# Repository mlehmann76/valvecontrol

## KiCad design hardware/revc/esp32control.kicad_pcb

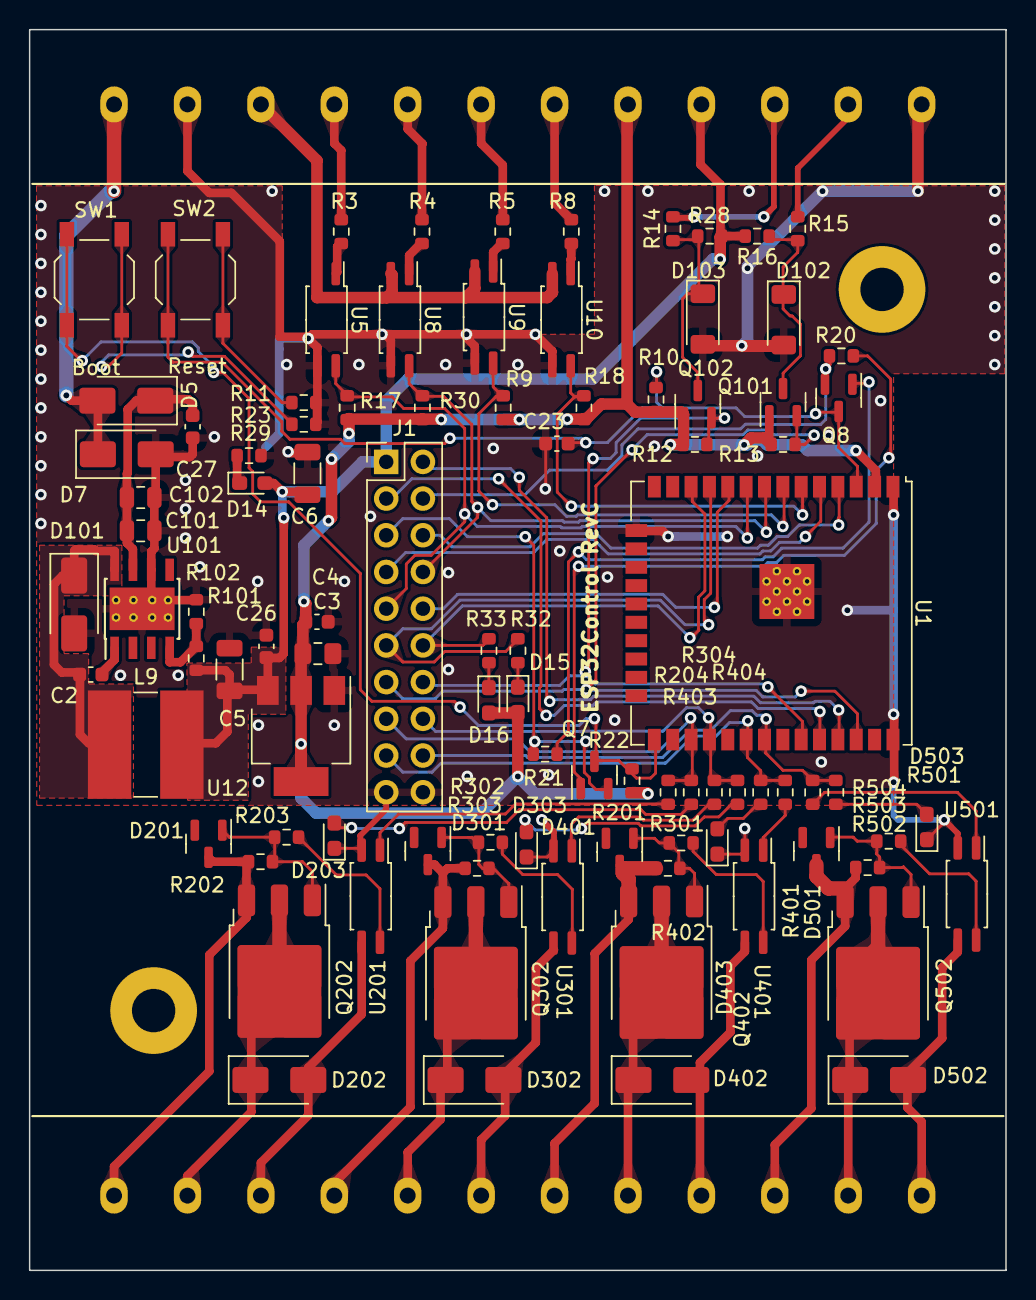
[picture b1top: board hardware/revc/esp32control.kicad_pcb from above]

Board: 2 copper layers, 67.6 x 85.9 mm, 95 parts (0 on the bottom side), 77 nets.

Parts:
C2: 10n 50V; C_0603_1608Metric
C3: 10u 25V; C_0805_2012Metric_Pad1.18x1.45mm_HandSolder
C4, C26, C27: 100n 50V; C_0603_1608Metric
C5, C6: 47u 10V; C_1206_3216Metric
C23: 1u 25V; C_0603_1608Metric
C101, C102: 10u 50V; C_0805_2012Metric
D5, D101, D202, D302, D402, D502: SS34; D_SMA
D7: SMAJ26CAQ; D_SMA
D14, D15, D16, D203, D303, D403, D503: red; LED_0603_1608Metric_Pad1.05x0.95mm_HandSolder
D102, D103: ZMM5V6-M; D_MiniMELF
D201, D301, D401, D501: BZX84C10; SOT-23
J1: Conn_02x10_Odd_Even; PinHeader_2x10_P2.54mm_Vertical
L9: 22u; L_Ferrocore_DLG-0705
Q7, Q8: MMBT3904; SOT-23
Q101, Q102: 2N7002; SOT-23
Q202, Q302, Q402, Q502: HSU4113; TO-252-3_TabPin2
R3, R4, R5, R8: 1k5; R_0603_1608Metric
R9, R10, R12, R13, R16, R17, R18, R20, R21, R22, R28, R30: 10k; R_0603_1608Metric
R11, R14, R15, R23: 100; R_0603_1608Metric
R29, R32, R33, R201, R202, R203, R204, R301, R302, R303, R304, R401, R402, R403, R404, R501, R502, R503, R504: 1k; R_0603_1608Metric
R101: 12k; R_0603_1608Metric
R102: 3k9; R_0603_1608Metric
SW1: Boot; SW_SPST_TL3342
SW2: Reset; SW_SPST_TL3342
U1: ESP32-WROOM; ESP32-WROOM-32UE
U5, U8, U9, U10, U201, U301, U401, U501: EL3H7; SOP-4_4.4x2.6mm_P1.27mm
U11: HUT4; CB_HUT_4
U12: AMS1117-3.3; SOT-223-3_TabPin2
U101: TPS5430DDA; TI_SO-PowerPAD-8_ThermalVias

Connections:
+3V3: C3.1, C4.1, D15.2 (A), D16.2 (A), Q101.1 (G), Q102.1 (G), R9.2, R10.2, R12.2, R13.2, R17.2, R18.2, R22.2, R30.2, U1.2 (3V3), U11.20, U12.2 (VO)
+5V: C5.1, C6.1, C26.1, D14.2 (A), J1.1, L9.2, R16.2, R28.2, R101.1, U11.21, U12.3 (VI)
+24V: C27.1, C101.1, C102.1, D5.1 (K), U101.7 (VIN)
/CH1: J1.15, R201.2, R204.2, U1.27 (IO16)
/CH2: J1.16, R301.2, R304.2, U1.28 (IO17)
/CH3: J1.17, R401.2, R404.2, U1.30 (IO18)
/CH4: J1.18, R501.2, R504.2, U1.31 (IO19)
/DTR: J1.5, Q7.2 (E), R21.1
/IN1: R3.2, U11.16
/IN2: R4.2, U11.17
/IN3: R5.2, U11.18
/IN4: R8.2, U11.19
/IO25: J1.10, U1.10 (IO25)
/IO26: J1.11, R32.1, U1.11 (IO26)
/IO27: J1.12, R33.1, U1.12 (IO27)
/IO32: J1.8, R30.1, U1.8 (IO32), U8.4
/IO33: J1.9, R17.1, U1.9 (IO33), U5.4
/IO34: R18.1, U1.6 (IO34), U10.4
/IO35: R9.1, U1.7 (IO35), U9.4
/IO36: J1.6, U1.4 (SENSOR_VP)
/IO39: J1.7, U1.5 (SENSOR_VN)
/OUT1: D202.1 (K), Q202.2 (D), U11.2
/OUT2: D302.1 (K), Q302.2 (D), U11.5
/OUT3: D402.1 (K), Q402.2 (D), U11.8
/OUT4: D502.1 (K), Q502.2 (D), U11.11
/PH: C2.2, D101.1 (K), L9.1, U101.8 (PH)
/RTS: J1.4, Q8.2 (E), R20.1
/RXD0: J1.3, U1.34 (RXD0)
/SCL: J1.13, Q101.2 (S), R13.1, U1.36 (IO22)
/SCL_EXT: D102.1 (K), Q101.3 (D), R15.1, R16.1
/SDA: J1.14, Q102.2 (S), R12.1, U1.33 (IO21)
/SDA_EXT: D103.1 (K), Q102.3 (D), R14.1, R28.1
/TXD0: J1.2, U1.35 (TXD0)
/dig_output/GNDA: D202.2 (A), U11.3, U201.3
/dig_output/Vin: D201.3 (K), Q202.3 (S), R202.1, U11.1
/nBoot: Q7.3 (C), R22.1, SW1.2, U1.25 (IO0)
/nReset: C23.1, Q8.3 (C), R10.1, SW2.2, U1.3 (EN)
/sheet5C1F9DE2/GNDA: D402.2 (A), U11.9, U401.3
/sheet5C1F9DE2/Vin: D401.3 (K), Q402.3 (S), R402.1, U11.7
/sheet5C1F9DE3/GNDA: D502.2 (A), U11.12, U501.3
/sheet5C1F9DE3/Vin: D501.3 (K), Q502.3 (S), R502.1, U11.10
/sheet5C1F370F/GNDA: D302.2 (A), U11.6, U301.3
/sheet5C1F370F/Vin: D301.3 (K), Q302.3 (S), R302.1, U11.4
GND: C3.2, C4.2, C5.2, C6.2, C23.2, C26.2, C27.2, C101.2, C102.2, D7.2, D101.2 (A), D102.2 (A), D103.2 (A), D203.1 (K), D303.1 (K), D403.1 (K), D503.1 (K), J1.19, J1.20, R11.2, R23.2, R29.1, R102.2, U1.1 (GND), U1.15 (GND), U1.38 (GND), U1.39 (GND-PAD), U5.3, U8.3, U9.3, U10.3, U11.14, U11.24, U12.1 (GND), U101.6 (GND), U101.9 (GNDPAD), U201.2, U301.2, U401.2, U501.2
unnamed: D14.1 (K), R29.2
unnamed: D15.1 (K), R32.2
unnamed: D16.1 (K), R33.2
unnamed: D201.1 (A), Q202.1 (G), R202.2, R203.2
unnamed: D203.2 (A), R204.1
unnamed: D301.1 (A), Q302.1 (G), R302.2, R303.2
unnamed: D303.2 (A), R304.1
unnamed: D401.1 (A), Q402.1 (G), R402.2, R403.2
unnamed: D403.2 (A), R404.1
unnamed: D501.1 (A), Q502.1 (G), R502.2, R503.2
unnamed: D503.2 (A), R504.1
unnamed: Q7.1 (B), R20.2
unnamed: Q8.1 (B), R21.2
unnamed: R3.1, U5.1
unnamed: R4.1, U8.1
unnamed: R5.1, U9.1
unnamed: R8.1, U10.1
unnamed: R11.1, SW2.1
unnamed: R14.2, U11.22
unnamed: R15.2, U11.23
unnamed: R23.1, SW1.1
unnamed: R201.1, U201.1
unnamed: R203.1, U201.4
unnamed: R301.1, U301.1
unnamed: R303.1, U301.4
unnamed: R401.1, U401.1
unnamed: R403.1, U401.4
unnamed: R501.1, U501.1
unnamed: R503.1, U501.4
unnamed: C2.1, U101.1 (BOOT)
unnamed: R101.2, R102.1, U101.4 (VSENSE)
VCOM: U5.2, U8.2, U9.2, U10.2, U11.15
VD: D5.2 (A), D7.1, U11.13

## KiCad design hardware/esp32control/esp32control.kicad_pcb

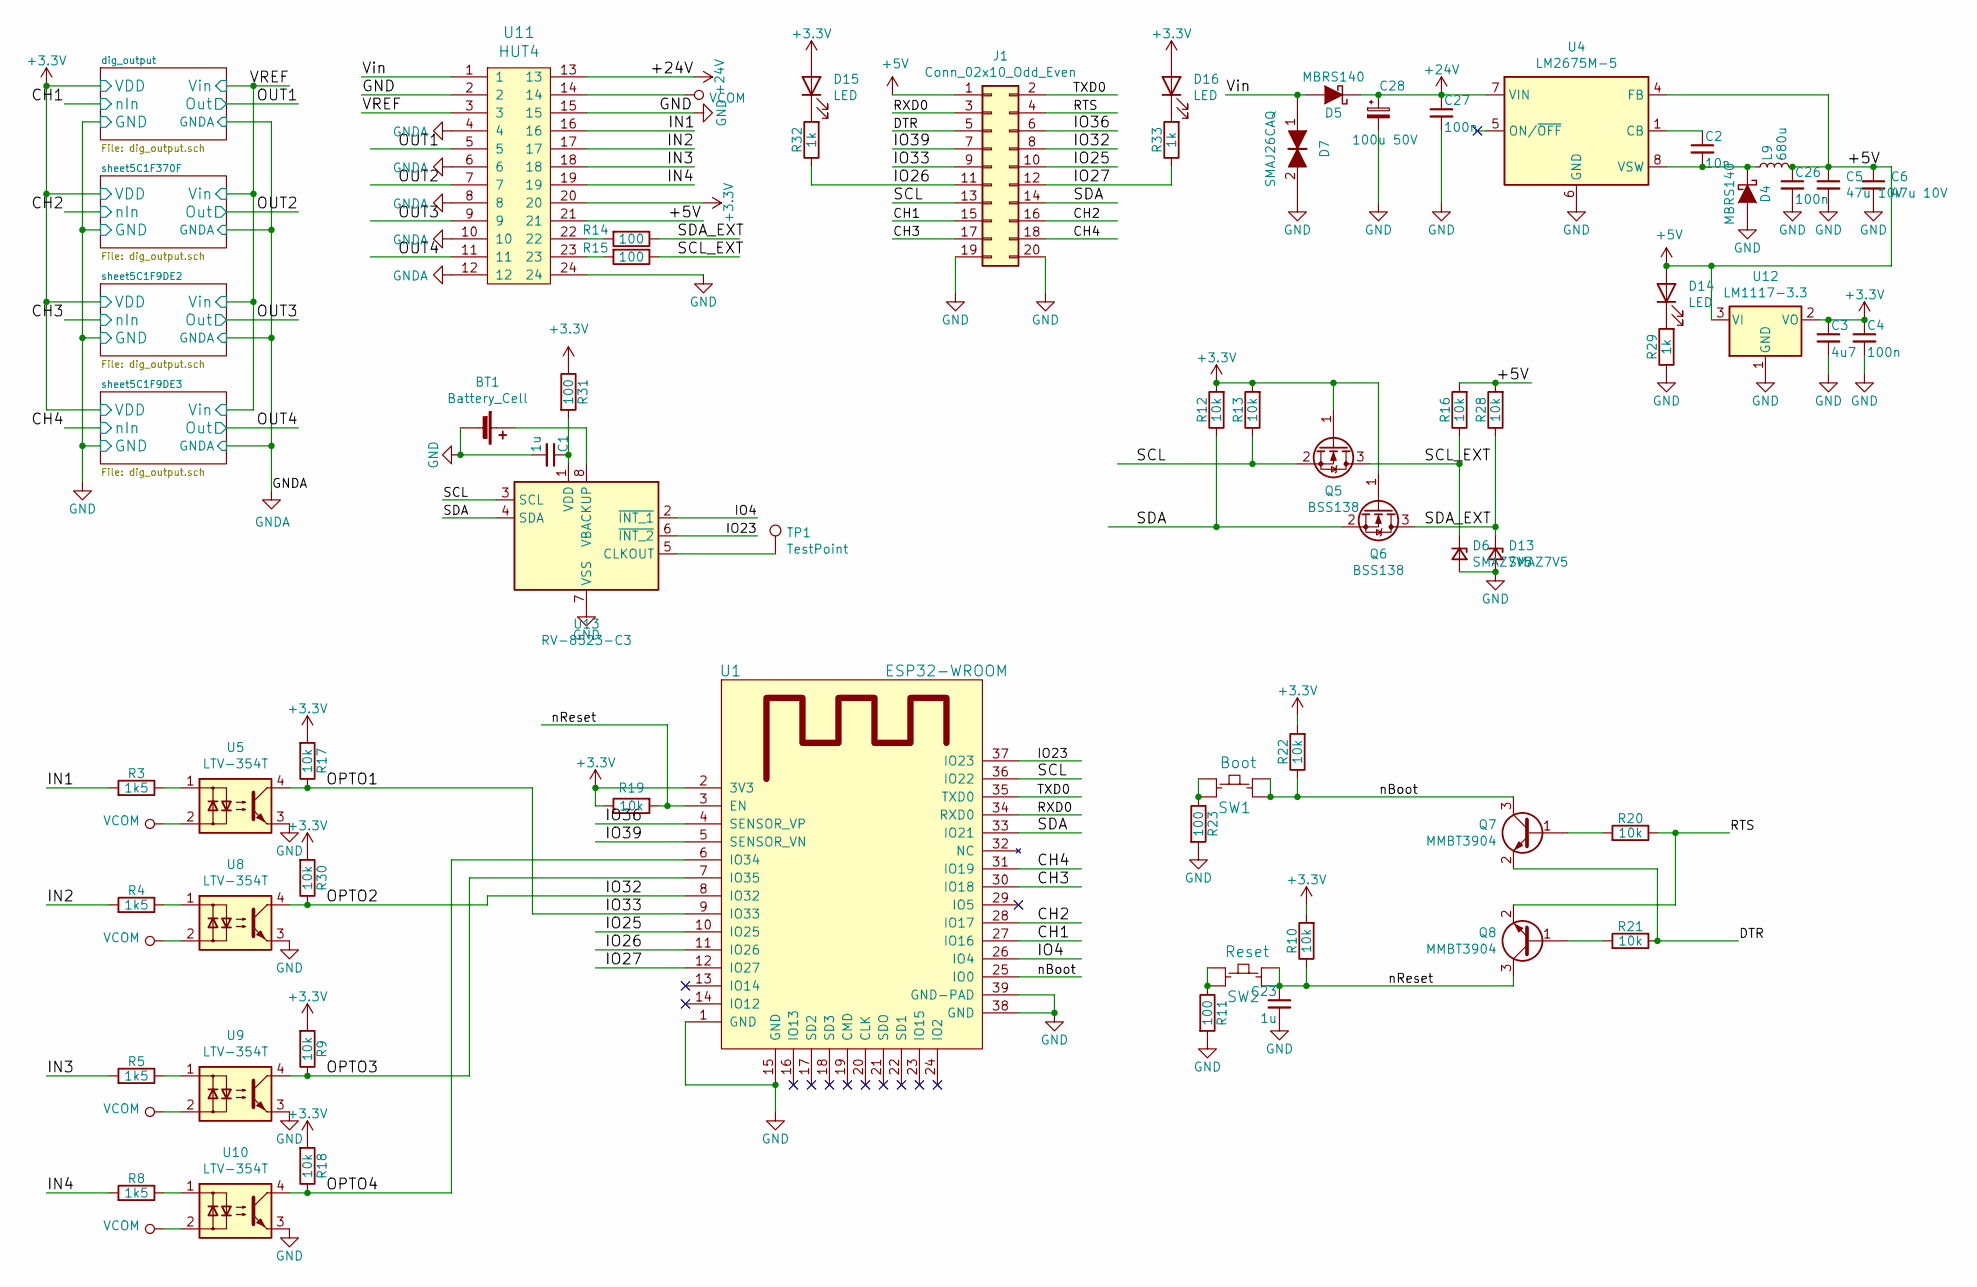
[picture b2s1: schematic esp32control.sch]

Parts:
BT1: Battery_Cell; BatteryHolder_Keystone_3001_1x12mm; Mouser 534-3001
C1, C23: 1u; C_0603_1608Metric
C2: 10n; C_0603_1608Metric
C3: 4u7; C_0805_2012Metric_Pad1.15x1.40mm_HandSolder
C4, C26, C27: 100n; C_0603_1608Metric
C5, C6: 47u 10V; C_1206_3216Metric
C28: 100u 50V; CP_Radial_D8.0mm_P3.50mm; Mouser 140-RGA101M1HBK0811G
D4, D5: MBRS140; D_SMA; Mouser 863-MBRS140T3G
D6, D13: SMAZ7V5; D_SMA; Mouser 621-SMAZ7V5-F
D7: SMAJ26CAQ; D_SMA; Mouser 621-SMAJ26CAQ-13-F
D14, D15, D16: LED; LED_0603_1608Metric_Pad1.05x0.95mm_HandSolder
J1: Conn_02x10_Odd_Even; PinHeader_2x10_P2.54mm_Vertical
L9: 680u; L_7.3x7.3_H4.5
Q5, Q6: BSS138; SOT-23; Mouser 771-BSS138P215
Q7, Q8: MMBT3904; SOT-23; Mouser 771-MMBT3904VL
R3, R4, R5, R8: 1k5; R_0603_1608Metric
R9, R10, R12, R13, R16, R17, R18, R19, R20, R21, R22, R28, R30: 10k; R_0603_1608Metric
R11, R14, R15, R23, R31: 100; R_0603_1608Metric
R29, R32, R33: 1k; R_0603_1608Metric
SW1: Boot; SMD_Switch_6.5x6; Mouser 667-EVQ-Q2B03W
SW2: Reset; SMD_Switch_6.5x6; Mouser 667-EVQ-Q2B03W
TP1: TestPoint; TestPoint_Pad_D1.5mm
U1: ESP32-WROOM
U4: LM2675M-5; SOIC-8_3.9x4.9mm_Pitch1.27mm; Mouser 926-LM2675M-5.0/NOPB
U5, U8, U9, U10: LTV-354T; SO-4_4.4x3.6mm_Pitch2.54mm; Mouser 859-LTV-354T
U11: HUT4; CB_HUT_4
U12: LM1117-3.3; SOT-223-3_TabPin2; Mouser 926-LM1117MP-3.3NOPB
U13: RV-8523-C3; RTC_SMD_MicroCrystal_C3_2.5x3.7mm; Mouser 428-201904-MG01

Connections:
+3V3: C3.1, C4.1, D15.2 (A), D16.2 (A), Q5.1 (G), Q6.1 (G), R9.2, R10.2, R12.2, R13.2, R17.2, R18.2, R19.1, R22.2, R30.2, R31.1, U1.2 (3V3), U11.20, U12.2 (VO); also elsewhere on the board
+5V: C5.1, C6.1, C26.1, D14.2 (A), J1.1, L9.2, R16.2, R28.2, U4.4 (FB), U11.21, U12.3 (VI)
+24V: C27.1, C28.1, D5.1 (K), U4.7 (VIN), U11.13
/CH1: J1.15, U1.27 (IO16); also elsewhere on the board
/CH2: J1.16, U1.28 (IO17); also elsewhere on the board
/CH3: J1.17, U1.30 (IO18); also elsewhere on the board
/CH4: J1.18, U1.31 (IO19); also elsewhere on the board
/DTR: J1.5, Q7.2 (E), R21.1
/IN1: R3.2, U11.16
/IN2: R4.2, U11.17
/IN3: R5.2, U11.18
/IN4: R8.2, U11.19
/IO4: U1.26 (IO4), U13.2 (~INT_1)
/IO23: U1.37 (IO23), U13.6 (~INT_2)
/IO25: J1.10, U1.10 (IO25)
/IO26: J1.11, R32.1, U1.11 (IO26)
/IO27: J1.12, R33.1, U1.12 (IO27)
/IO32: J1.8, R30.1, U1.8 (IO32), U8.4
/IO33: J1.9, R17.1, U1.9 (IO33), U5.4
/IO36: J1.6, U1.4 (SENSOR_VP)
/IO39: J1.7, U1.5 (SENSOR_VN)
/OPTO3: R9.1, U1.7 (IO35), U9.4
/OPTO4: R18.1, U1.6 (IO34), U10.4
/OUT1: U11.5; also elsewhere on the board
/OUT2: U11.7; also elsewhere on the board
/OUT3: U11.9; also elsewhere on the board
/OUT4: U11.11; also elsewhere on the board
/RTS: J1.4, Q8.2 (E), R20.1
/RXD0: J1.3, U1.34 (RXD0)
/SCL: J1.13, Q5.2 (S), R13.1, U1.36 (IO22), U13.3 (SCL)
/SCL_EXT: D6.1 (K), Q5.3 (D), R15.1, R16.1
/SDA: J1.14, Q6.2 (S), R12.1, U1.33 (IO21), U13.4 (SDA)
/SDA_EXT: D13.1 (K), Q6.3 (D), R14.1, R28.1
/TXD0: J1.2, U1.35 (TXD0)
/VREF: U11.3; also elsewhere on the board
/Vin: D5.2 (A), D7.1, U11.1
/nBoot: Q7.3 (C), R22.1, SW1.B, SW1.B', U1.25 (IO0)
/nReset: C23.1, Q8.3 (C), R10.1, R19.2, SW2.B, SW2.B', U1.3 (EN)
GND: BT1.2 (-), C1.2, C3.2, C4.2, C5.2, C6.2, C23.2, C26.2, C27.2, C28.2, D4.2 (A), D6.2 (A), D7.2, D13.2 (A), J1.19, J1.20, R11.2, R23.2, R29.1, U1.1 (GND), U1.15 (GND), U1.38 (GND), U1.39 (GND-PAD), U4.6 (GND), U5.3, U8.3, U9.3, U10.3, U11.2, U11.15, U11.24, U12.1 (GND), U13.7 (VSS); also elsewhere on the board
GNDA: U11.4, U11.6, U11.8, U11.10, U11.12; also elsewhere on the board
unnamed: BT1.1 (+), U13.8 (VBACKUP)
unnamed: C1.1, R31.2, U13.1 (VDD)
unnamed: C2.1, U4.1 (CB)
unnamed: C2.2, D4.1 (K), L9.1, U4.8 (VSW)
unnamed: D14.1 (K), R29.2
unnamed: D15.1 (K), R32.2
unnamed: D16.1 (K), R33.2
unnamed: Q7.1 (B), R20.2
unnamed: Q8.1 (B), R21.2
unnamed: R3.1, U5.1
unnamed: R4.1, U8.1
unnamed: R5.1, U9.1
unnamed: R8.1, U10.1
unnamed: R11.1, SW2.A, SW2.A'
unnamed: R14.2, U11.22
unnamed: R15.2, U11.23
unnamed: R23.1, SW1.A, SW1.A'
unnamed: TP1.1, U13.5 (CLKOUT)
VCOM: U5.2, U8.2, U9.2, U10.2, U11.14

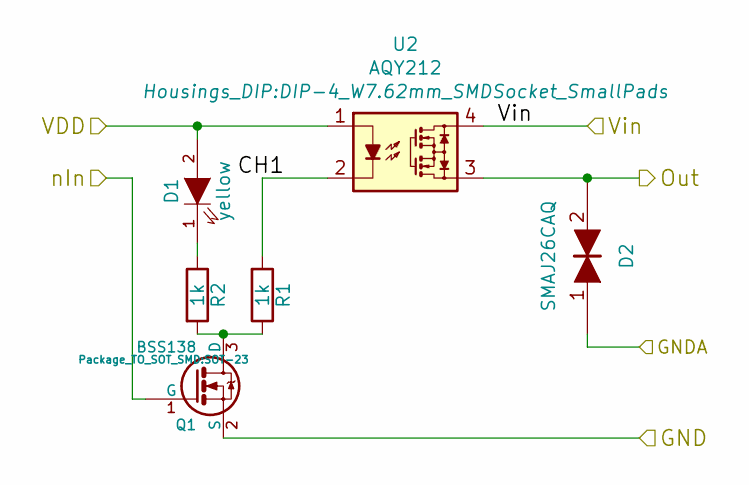
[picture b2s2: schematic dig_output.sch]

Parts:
D1: yellow; LED_0603_HandSoldering; Mouser 710-150060YS75000
D2: SMAJ26CAQ; D_SMA; Mouser 621-SMAJ26CAQ-13-F
Q1: BSS138; SOT-23; Mouser 771-BSS138P215
R1, R2: 1k; R_0603_1608Metric
U2: AQY212; DIP-4_W7.62mm_SMDSocket_SmallPads; Mouser 769-AQY212GS

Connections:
+3V3: D1.2 (A), U2.1; also elsewhere on the board
/CH1: Q1.1 (G); also elsewhere on the board
/OUT1: D2.2, U2.3; also elsewhere on the board
/VREF: U2.4; also elsewhere on the board
GND: Q1.2 (S); also elsewhere on the board
GNDA: D2.1; also elsewhere on the board
unnamed: D1.1 (K), R2.1
unnamed: Q1.3 (D), R1.1, R2.2
unnamed: R1.2, U2.2

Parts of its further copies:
D8, D10, D12: SMAJ26CAQ; D_SMA; Mouser 621-SMAJ26CAQ-13-F
Q2, Q3, Q4: BSS138; SOT-23; Mouser 771-BSS138P215
R6, R7, R24, R25, R26, R27: 1k; R_0603_1608Metric
U3, U6, U7: AQY212; DIP-4_W7.62mm_SMDSocket_SmallPads; Mouser 769-AQY212GS

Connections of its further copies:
+3V3: U3.1, U6.1, U7.1; also elsewhere on the board
/CH2: Q2.1 (G); also elsewhere on the board
/CH3: Q3.1 (G); also elsewhere on the board
/CH4: Q4.1 (G); also elsewhere on the board
/OUT2: D8.2, U3.3; also elsewhere on the board
/OUT3: D10.2, U6.3; also elsewhere on the board
/OUT4: D12.2, U7.3; also elsewhere on the board
/VREF: U3.4, U6.4, U7.4; also elsewhere on the board
GND: Q2.2 (S), Q3.2 (S), Q4.2 (S); also elsewhere on the board
GNDA: D8.1, D10.1, D12.1; also elsewhere on the board
unnamed 45: R7.1; also elsewhere on the board
unnamed 46: R25.1; also elsewhere on the board
unnamed 47: R27.1; also elsewhere on the board
unnamed: Q2.3 (D), R6.1, R7.2
unnamed: Q3.3 (D), R24.1, R25.2
unnamed: Q4.3 (D), R26.1, R27.2
unnamed: R6.2, U3.2
unnamed: R24.2, U6.2
unnamed: R26.2, U7.2

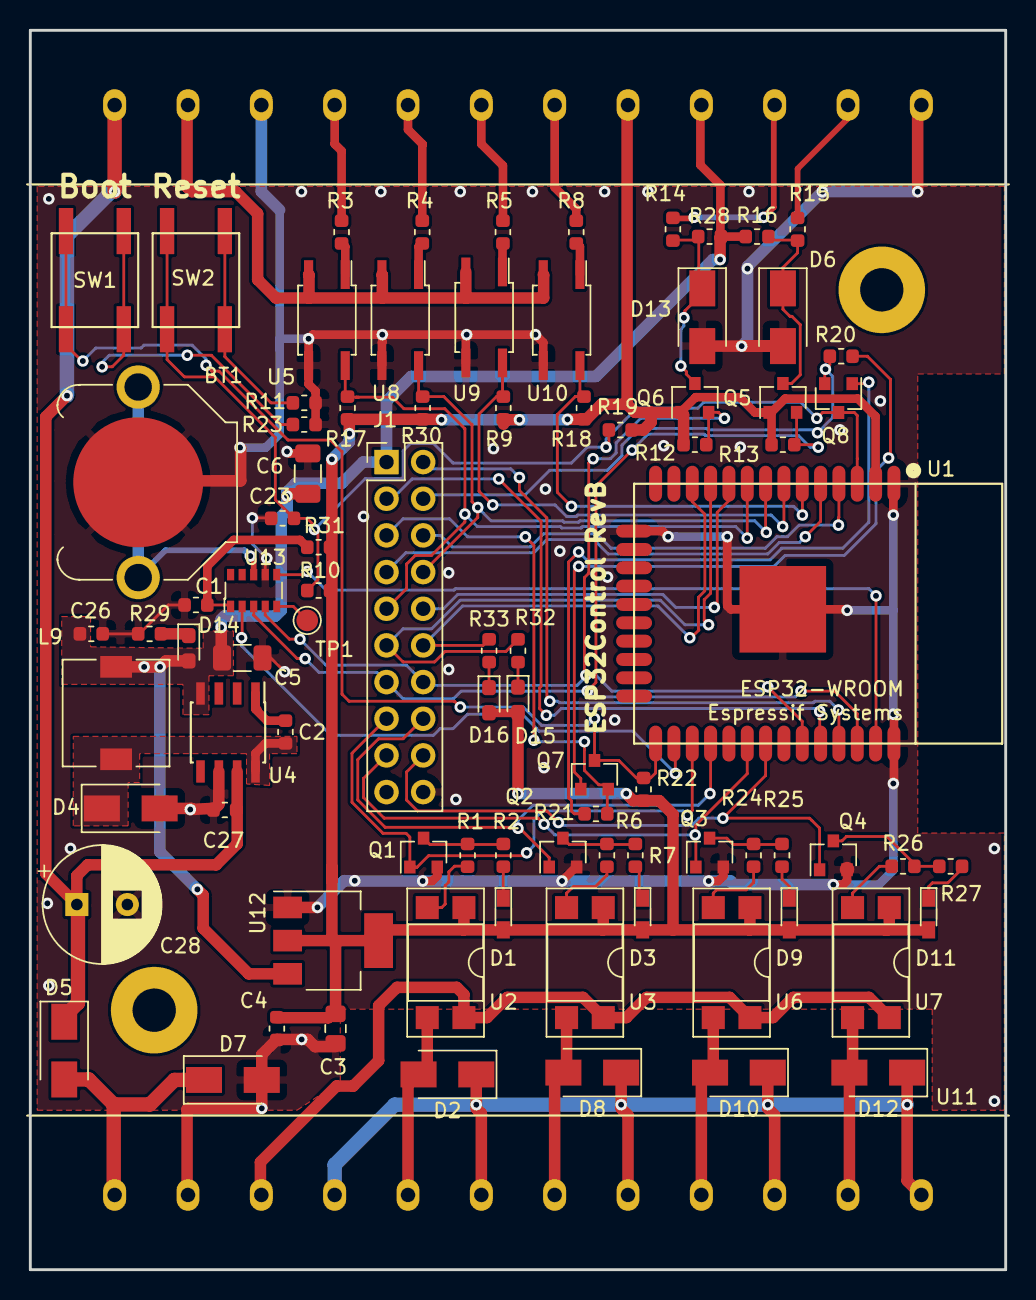
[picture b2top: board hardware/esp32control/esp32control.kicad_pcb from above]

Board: 2 copper layers, 67.6 x 85.9 mm, 86 parts (0 on the bottom side), 71 nets.

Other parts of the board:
D3, D9, D11: LED; LED_0603_HandSoldering

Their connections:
+3V3: D3.2, D9.2, D11.2; also elsewhere on the board
unnamed 45: D3.1; also elsewhere on the board
unnamed 46: D9.1; also elsewhere on the board
unnamed 47: D11.1; also elsewhere on the board

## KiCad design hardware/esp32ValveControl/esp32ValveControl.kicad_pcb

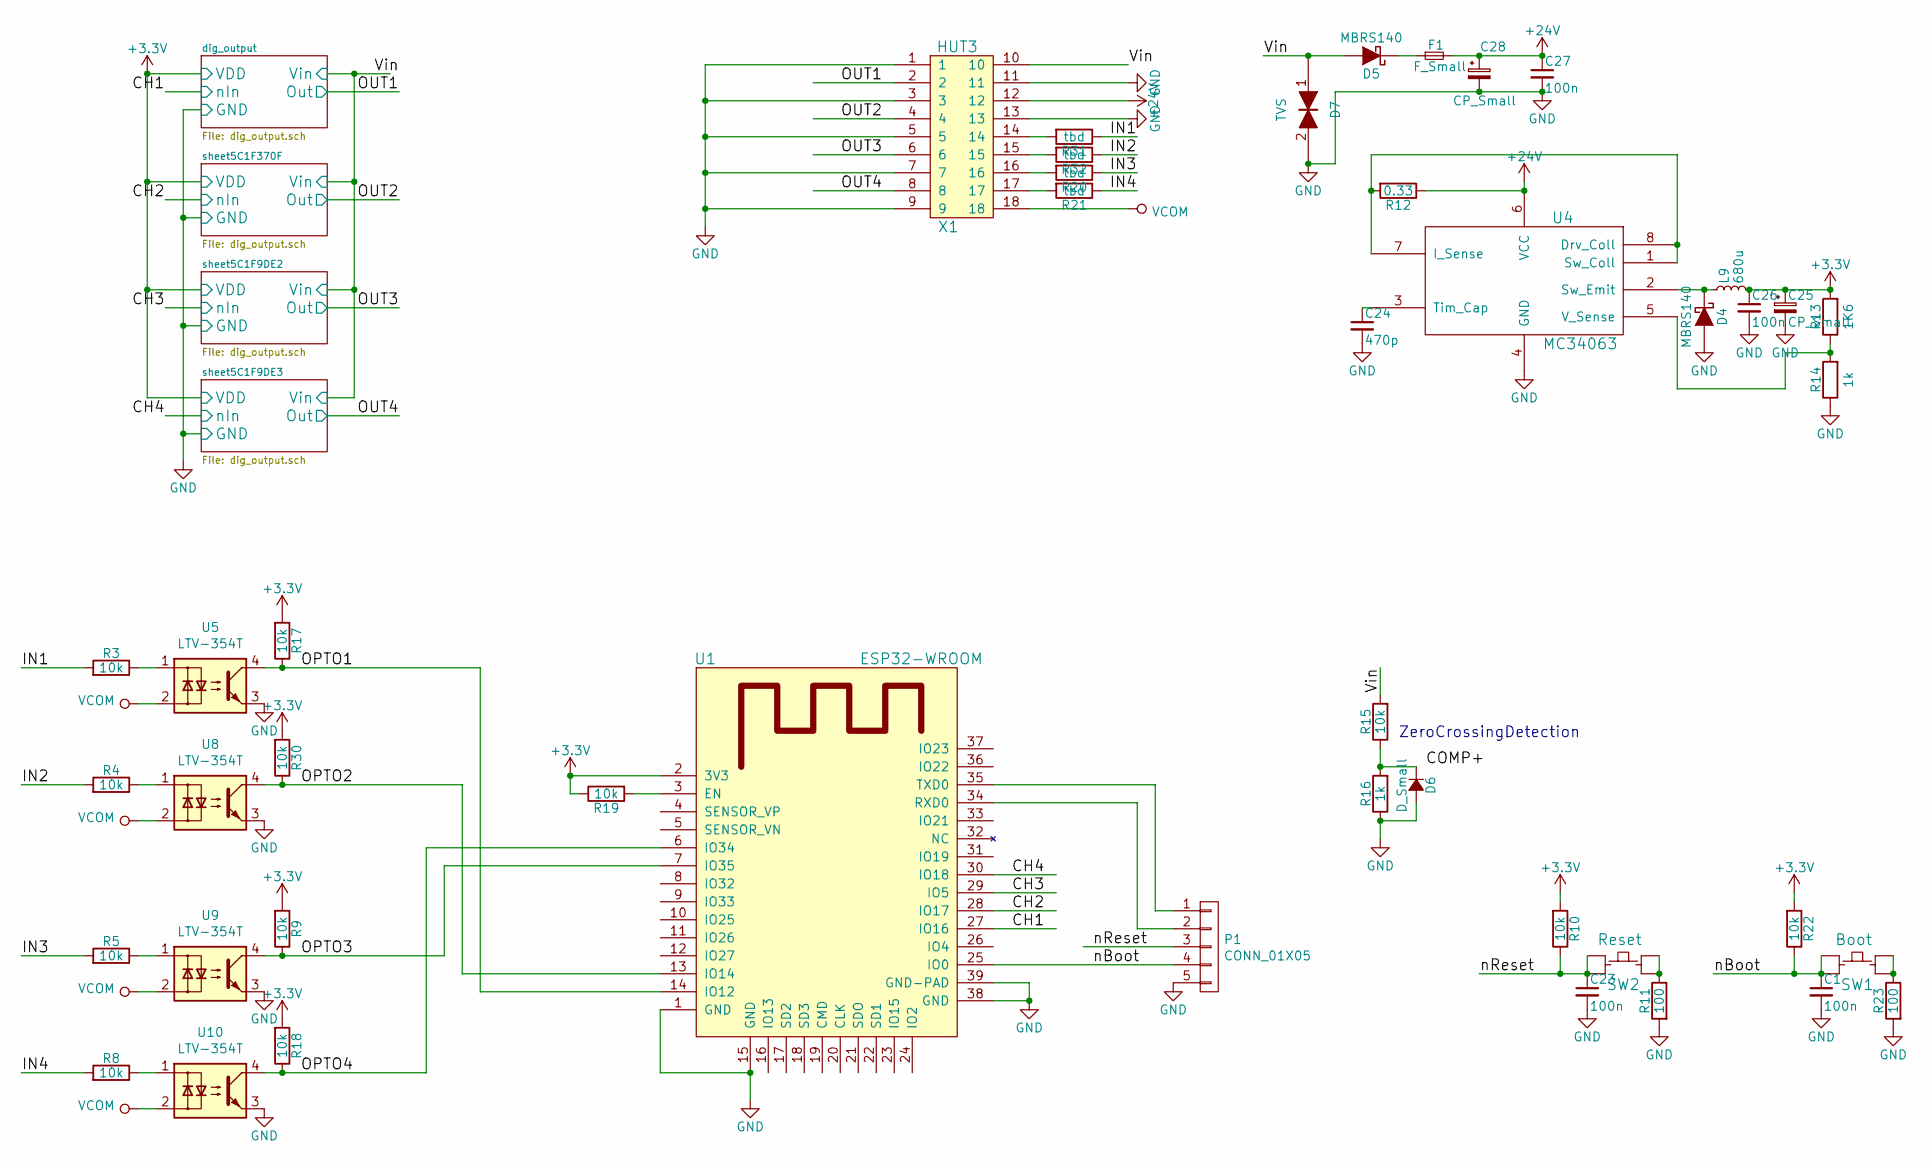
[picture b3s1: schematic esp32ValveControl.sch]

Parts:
C1, C23, C26, C27: 100n; C_0603
C24: 470p; C_0603
C25, C28: CP_Small; C_Radial_D8_L11.5_P3.5
D4, D5: MBRS140; D_SMA
D6: D_Small; MiniMELF_Standard
D7: TVS; D_SMA
F1: F_Small; Fuse_SMD1206_Wave
L9: 680u; WE-PD-7345
P1: CONN_01X05; Pin_Header_Straight_1x05_Pitch2.54mm
R3, R4, R5, R8, R9, R10, R15, R17, R18, R19, R22, R30: 10k; R_0603
R11, R23: 100; R_0603
R12: 0.33; R_1206
R13: 1K6; R_0603
R14, R16: 1k; R_0603
R20, R21, R31, R32: tbd; R_0603
SW1: Boot; SMD_Switch_6.5x6
SW2: Reset; SMD_Switch_6.5x6
U1: ESP32-WROOM
U4: MC34063; SOIC-8_3.9x4.9mm_Pitch1.27mm
U5, U8, U9, U10: LTV-354T; SO-4_4.4x3.6mm_Pitch2.54mm
X1: HUT3; CB_HUT_3

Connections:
+3V3: C25.1, C26.1, L9.2, R9.2, R10.2, R13.2, R17.2, R18.2, R19.1, R22.2, R30.2, U1.2 (3V3); also elsewhere on the board
+24V: C27.1, C28.1, F1.2, R12.1, U4.6 (VCC), X1.12
/CH1: U1.27 (IO16); also elsewhere on the board
/CH2: U1.28 (IO17); also elsewhere on the board
/CH3: U1.29 (IO5); also elsewhere on the board
/CH4: U1.30 (IO18); also elsewhere on the board
/IN1: R3.2, R31.1
/IN2: R4.2, R32.1
/IN3: R5.2, R20.1
/IN4: R8.2, R21.1
/OPTO1: R17.1, U1.14 (IO12), U5.4
/OPTO2: R30.1, U1.13 (IO14), U8.4
/OPTO3: R9.1, U1.7 (IO35), U9.4
/OPTO4: R18.1, U1.6 (IO34), U10.4
/OUT1: X1.2; also elsewhere on the board
/OUT2: X1.4; also elsewhere on the board
/OUT3: X1.6; also elsewhere on the board
/OUT4: X1.8; also elsewhere on the board
/Vin: D5.2 (A), D7.1, R15.2, X1.10
/nBoot: C1.1, P1.4, R22.1, SW1.B, SW1.B', U1.25 (IO0)
/nReset: C23.1, P1.3, R10.1, SW2.B, SW2.B'
GND: C1.2, C23.2, C24.2, C25.2, C26.2, C27.2, C28.2, D4.2 (A), D6.2 (A), D7.2, P1.5, R11.2, R14.1, R16.1, R23.2, U1.1 (GND), U1.15 (GND), U1.38 (GND), U1.39 (GND-PAD), U4.4 (GND), U5.3, U8.3, U9.3, U10.3, X1.1, X1.3, X1.5, X1.7, X1.9, X1.11, X1.13; also elsewhere on the board
unnamed: C24.1, U4.3 (Tim_Cap)
unnamed: D4.1 (K), L9.1, U4.2 (Sw_Emit)
unnamed: D5.1 (K), F1.1
unnamed: D6.1 (K), R15.1, R16.2
unnamed: P1.1, U1.35 (TXD0)
unnamed: P1.2, U1.34 (RXD0)
unnamed: R3.1, U5.1
unnamed: R4.1, U8.1
unnamed: R5.1, U9.1
unnamed: R8.1, U10.1
unnamed: R11.1, SW2.A, SW2.A'
unnamed: R12.2, U4.1 (Sw_Coll), U4.7 (I_Sense), U4.8 (Drv_Coll)
unnamed: R13.1, R14.2, U4.5 (V_Sense)
unnamed: R19.2, U1.3 (EN)
unnamed: R20.2, X1.16
unnamed: R21.2, X1.17
unnamed: R23.1, SW1.A, SW1.A'
unnamed: R31.2, X1.14
unnamed: R32.2, X1.15
VCOM: U5.2, U8.2, U9.2, U10.2, X1.18

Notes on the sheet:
ZeroCrossingDetection

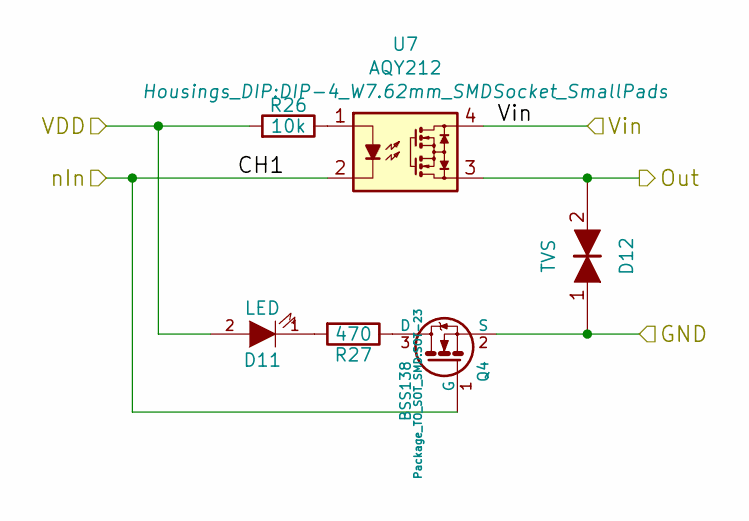
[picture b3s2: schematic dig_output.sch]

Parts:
D1: LED; LED_0603_HandSoldering
D2: TVS; D_SMA
Q1: BSS138; SOT-23
R1: 10k; R_0603
R2: 470; R_0603
U2: AQY212; DIP-4_W7.62mm_SMDSocket_SmallPads

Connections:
+3V3: D1.2 (A), R1.2; also elsewhere on the board
/CH1: Q1.1 (G), U2.2; also elsewhere on the board
/OUT1: D2.2, U2.3; also elsewhere on the board
/dig_output/Vin: U2.4; also elsewhere on the board
GND: D2.1, Q1.2 (S); also elsewhere on the board
unnamed: D1.1 (K), R2.2
unnamed: Q1.3 (D), R2.1
unnamed: R1.1, U2.1

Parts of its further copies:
D3, D9, D11: LED; LED_0603_HandSoldering
D8, D10, D12: TVS; D_SMA
Q2, Q3, Q4: BSS138; SOT-23
R6, R24, R26: 10k; R_0603
R7, R25, R27: 470; R_0603
U3, U6, U7: AQY212; DIP-4_W7.62mm_SMDSocket_SmallPads

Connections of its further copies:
+3V3: D3.2 (A), D9.2 (A), D11.2 (A), R6.2, R24.2, R26.2; also elsewhere on the board
/CH2: Q2.1 (G), U3.2; also elsewhere on the board
/CH3: Q3.1 (G), U6.2; also elsewhere on the board
/CH4: Q4.1 (G), U7.2; also elsewhere on the board
/OUT2: D8.2, U3.3; also elsewhere on the board
/OUT3: D10.2, U6.3; also elsewhere on the board
/OUT4: D12.2, U7.3; also elsewhere on the board
/dig_output/Vin: U3.4, U6.4, U7.4; also elsewhere on the board
GND: D8.1, D10.1, D12.1, Q2.2 (S), Q3.2 (S), Q4.2 (S); also elsewhere on the board
unnamed: D3.1 (K), R7.2
unnamed: D9.1 (K), R25.2
unnamed: D11.1 (K), R27.2
unnamed: Q2.3 (D), R7.1
unnamed: Q3.3 (D), R25.1
unnamed: Q4.3 (D), R27.1
unnamed: R6.1, U3.1
unnamed: R24.1, U6.1
unnamed: R26.1, U7.1

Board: 2 copper layers, 69 parts (0 on the bottom side), 55 nets, no tracks yet.

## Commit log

2018-05-07 initial
2018-05-11 change to esp32mqtt
2018-05-11 old mqtt files removed
2018-05-12 corrected pin names according to hardware bug in gpiotask, changed updateGpio change status messages to son/soff to prevent false enabling enabled reboot on panic
2018-05-25 corrected status message request answer
2018-06-26 changed topic names
2018-06-28 split mqtt to mqtt_user
2018-06-29 add base85 decoder
2018-06-29 add upload.py test
2018-08-17 esp32ValveControl hardware initial
2018-08-21 schem_/pcb update
2018-10-13 changed ota handling, added udp
2018-10-13 hardware update
2018-10-19 changed control format to json strings
2018-10-21 added base85 decode and md5 checksum gen. for ota data
2018-10-22 added firmware-update json message decoder
2018-10-24 added esp_ota commands
2018-10-25 add ota/mqtt task messages, working mqtt-ota update
2018-10-27 added preliminary config on nvs
2018-10-29 added test http server for config, mqtt config rework
2018-10-30 added config with json over http setup
2018-10-31 refaktor, cleanup, added wps button short/long detect
2018-11-07 clean up, separated mqtt from main
2018-11-19 firmware to submodule
2018-12-16 libs update
2018-12-25 hier. schematic updates
2018-12-28 route and fab files
2019-04-01 pcb update
2019-04-03 updated sch & pcb
2019-06-02 rename
2020-03-30 silk update, fab files regen, pdf added
2020-05-21 revB initial
2020-05-22 pcb update, fab generated
2020-05-23 added pdf outputs, regen fab
2020-05-23 changed gerber output to jlcpcb format
2020-05-24 switched position of con and esp in layout
2020-05-24 moved via out of pad
2020-05-24 corrected silk screen
2020-06-05 bom update
2022-08-17 moved to github
2022-08-18 kicad6 update
2022-08-18 add backups to ignore
2023-11-12 renamed hw to revb
2023-11-12 revc
2023-11-12 rename kibot file
2023-11-12 update workflow file
2023-11-13 remove inner layer in yaml
2023-11-13 fixed erc
2023-11-13 fixed drc
2023-11-13 updated wroom32 fp
2023-11-13 updated kibot
2023-11-13 updated pcb
2023-11-13 updated yml
2023-11-13 yml updates
2023-11-13 fixed layer entries
2023-11-14 updated sch, pcb, bom
2023-11-14 reduced drc verbosity
2023-11-15 workflow fix (#2)
    * remove inner layer in yaml
    * fixed erc
    * fixed drc
    * updated wroom32 fp
    * updated kibot
    * updated pcb
